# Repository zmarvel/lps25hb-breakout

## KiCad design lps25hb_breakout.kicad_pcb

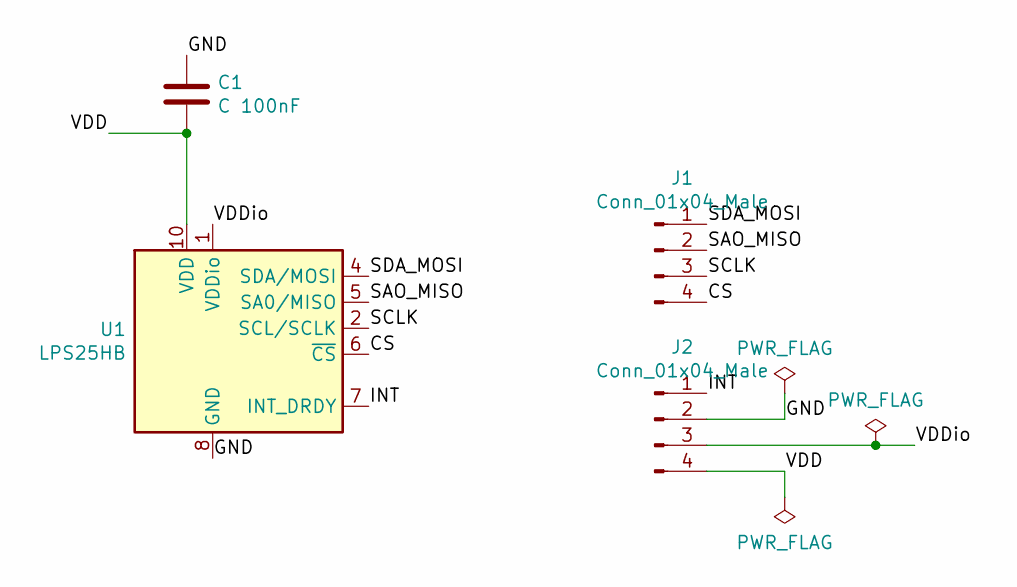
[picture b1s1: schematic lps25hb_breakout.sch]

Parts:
C1: C 100nF; C_1206_HandSoldering
J1, J2: Conn_01x04_Male; Pin_Header_Straight_1x04_Pitch2.54mm
U1: LPS25HB; ST_HLGA-10_2.5x2.5mm_P0.6mm_LayoutBorder3x2y_HandSolder

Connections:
/CS: J1.4, U1.6 (~CS)
/GND: C1.1, J2.2, U1.3 (GND), U1.8 (GND), U1.9 (GND)
/INT: J2.1, U1.7 (INT_DRDY)
/SAO_MISO: J1.2, U1.5 (SA0/MISO)
/SCLK: J1.3, U1.2 (SCL/SCLK)
/SDA_MOSI: J1.1, U1.4 (SDA/MOSI)
/VDD: C1.2, J2.4, U1.10 (VDD)
/VDDio: J2.3, U1.1 (VDDio)

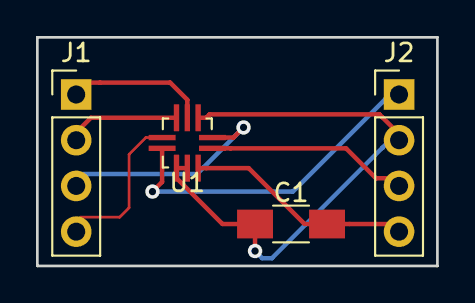
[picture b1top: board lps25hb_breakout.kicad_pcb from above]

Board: 2 copper layers, 22.2 x 12.7 mm, 4 parts (0 on the bottom side), 8 nets.
